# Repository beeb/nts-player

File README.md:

# NTS Web Radio Player

This is a standalone Wi-Fi connected web-radio player based on ESP-32. It was designed for the
[NTS.live](https://www.nts.live/) radio which has 18 live stations (2 main channels + 16 infinite mixtapes).

It's built around the ESP32-S3 and a PCM5122 DAC, with firmware written in Rust and a 3D-printed enclosure. The design
is made to be very simple to interact with: a single encoder with a large knob to select the station and change the
volume.

A ring of LEDs show which station is selected and the current volume level. The click action of the encoder switches
between the modes and allows to put the device to sleep.

Note: this device is not affiliated with NTS or Atonemo which have created a standalone player for NTS. Support your
favorite radio by [becoming a supporter](https://www.nts.live/supporters) or
[buying from the shop](https://shop.nts.live/).

## Features

- Streams MP3 web radio over HTTPS (e.g. NTS: 256 kbps, 44.1 kHz stereo)
- 18 stations on one detented encoder, one click per station
- 18-LED ring around the knob shows the current station (and volume in volume mode)
- Push the knob to toggle station / volume mode, long-press to sleep, press to wake
- Hold the devkit boot button for 5 s to erase all settings (Wi-Fi included) and restart
- Line out at up to about 1.5 Vrms on 3.5 mm and RCA, wired in parallel
  - This is meant as line out, not as headphones output, it expects a load of 1 kOhm or more.
  - The DAC can reach 2.1 Vrms, but the firmware limits the top volume step to -3 dB.
- Low sleep current (about 0.6 mA at 5 V): LED ring and DAC are power-switched in deep sleep
- Home Assistant "off" is a standby that keeps Wi-Fi on and breathes the station LED dimly, press the knob or turn it on
  in HA to wake
- Powered over USB-C (5 V)
- Wi-Fi setup through a portal on the `nts-player` access point
- Home Assistant control (power, station, volume) through the built-in ESPHome integration
- Firmware updates over Wi-Fi from a page on the device, with automatic rollback if the new firmware fails to start

## Repository Layout

```text
firmware/   Rust firmware (ESP-IDF, std)
kicad/      KiCad schematic and PCB for the carrier board
enclosure/  3d-printable enclosure parts
docs/       Datasheet links and devkit pinout
```

## Pin Map

| Function                                              | GPIO      |
| ----------------------------------------------------- | --------- |
| DAC XSMT (soft mute, 10k pull-down)                   | 4         |
| I2S BCK / DIN / LRCK                                  | 5 / 6 / 7 |
| I2C SDA / SCL (4.7k pull-ups to always-on 3V3)        | 8 / 9     |
| Encoder A / B                                         | 10 / 11   |
| Encoder push (wake pin, 10k pull-up to always-on 3V3) | 12        |
| LED ring power enable (10k pull-down)                 | 13        |
| DAC LDO enable (10k pull-down)                        | 14        |
| LED data (via level shifter)                          | 21        |

Avoided: strapping pins 0, 3, 45, 46; GPIO35–37 (octal PSRAM); GPIO19/20 (USB); GPIO38 (onboard RGB LED); GPIO43/44
(UART0).

## Building and Flashing

This is a `std` (ESP-IDF based) Rust project. The ESP-IDF C SDK is downloaded and built automatically by the
`esp-idf-sys` build script. Run all commands from the repository root.

### Prerequisites with Nix

The [flake](./flake.nix) provides a dev shell (x86_64 Linux only) with the Xtensa Rust toolchain from esp-rs (pinned in
[`nix/esp-rust.nix`](./nix/esp-rust.nix)), `ldproxy`, `espflash`, `just`, `jq` and the tools needed by the ESP-IDF
build:

```sh
nix develop
```

### Prerequisites without Nix

Espressif's [Rust on ESP book](https://docs.espressif.com/projects/rust/book/getting-started/index.html) is the
reference for the toolchain setup. TL;DR:

1. Install the
   [ESP-IDF host dependencies](https://docs.espressif.com/projects/esp-idf/en/stable/esp32s3/get-started/linux-macos-setup.html#step-1-install-prerequisites)

2. Install [Rust with `rustup`](https://rustup.rs/).

3. Install [`espup`](https://github.com/esp-rs/espup) and the Xtensa toolchain:

   ```sh
   cargo install espup --locked
   espup install
   ```

4. Activate the environment from `espup`. **This has to be done in every new shell**:

   ```sh
   . $HOME/export-esp.sh
   ```

5. Install the linker wrapper, the flashing tool and the command runner:

   ```sh
   cargo install ldproxy --locked
   cargo install espflash --locked
   cargo install just --locked
   ```

   `ldproxy` is the linker set in [`.cargo/config.toml`](./.cargo/config.toml). Also install `jq` with your package
   manager. `just` runs the commands below, `jq` reads the version in `just export`.

### ESP-IDF

The version is pinned in [`.cargo/config.toml`](./.cargo/config.toml):

```toml
[env]
ESP_IDF_VERSION = "v5.5.5"
```

On the first `cargo build`, the `esp-idf-sys` build script clones that tag into `.embuild/` and downloads the matching
ESP-IDF toolchains. This will take a few GBs of space and take a while the first time.

### Build

```sh
just build
```

Run `just` alone to list all commands.

### Flash and Monitor

Connect the board over USB, then:

```sh
just flash
```

This builds the release firmware, flashes it and opens the serial monitor. `cargo run` does the same through the cargo
`runner` in [`.cargo/config.toml`](./.cargo/config.toml), which calls `just flash-elf`. That recipe also writes the
bootloader built by ESP-IDF (it has app rollback enabled) and the partition table in
[`firmware/partitions.csv`](./firmware/partitions.csv). Plain `espflash flash <elf>` would write espflash's own
bootloader and table and break updates over Wi-Fi. `just monitor` opens the monitor without flashing.

### WSL

Pass the board through to WSL with [usbipd-win](https://github.com/dorssel/usbipd-win). In PowerShell:

```powershell
usbipd list                                         # find the board's bus ID
usbipd bind --busid <BUSID>                         # once, as administrator
usbipd attach --wsl --busid <BUSID> --auto-attach   # each session
```

Your WSL user must be in the `dialout` group to open `/dev/ttyACM0`.

## Firmware Updates over Wi-Fi

### Making a release

1. Bump `version` in [`firmware/Cargo.toml`](./firmware/Cargo.toml).
2. Run `just export`. It builds the release firmware and saves `nts-player-<version>.bin` at the repository root.
3. Send that file.

### Updating a player

1. On the same Wi-Fi as the player, open <http://nts-player.local/>. If the name doesn't resolve, use the IP address of
   the ESP32.
2. Pick the `.bin` file and click Upload. Keep the page open.
3. Playback stops and the LED ring fills up in green. The player restarts with the new firmware, and the page shows the
   new version.

The page rejects files that are not a valid firmware. If the new firmware fails before it connects to Wi-Fi, the next
restart rolls back to the old firmware.

## License

- Hardware (`kicad/`) and enclosure (`enclosure/`): [CC BY-NC-SA 4.0](LICENSE-CC-BY-NC-SA)
- Firmware (`firmware/`): dual-licensed under [MIT](LICENSE-MIT) or [Apache-2.0](LICENSE-APACHE), at your option

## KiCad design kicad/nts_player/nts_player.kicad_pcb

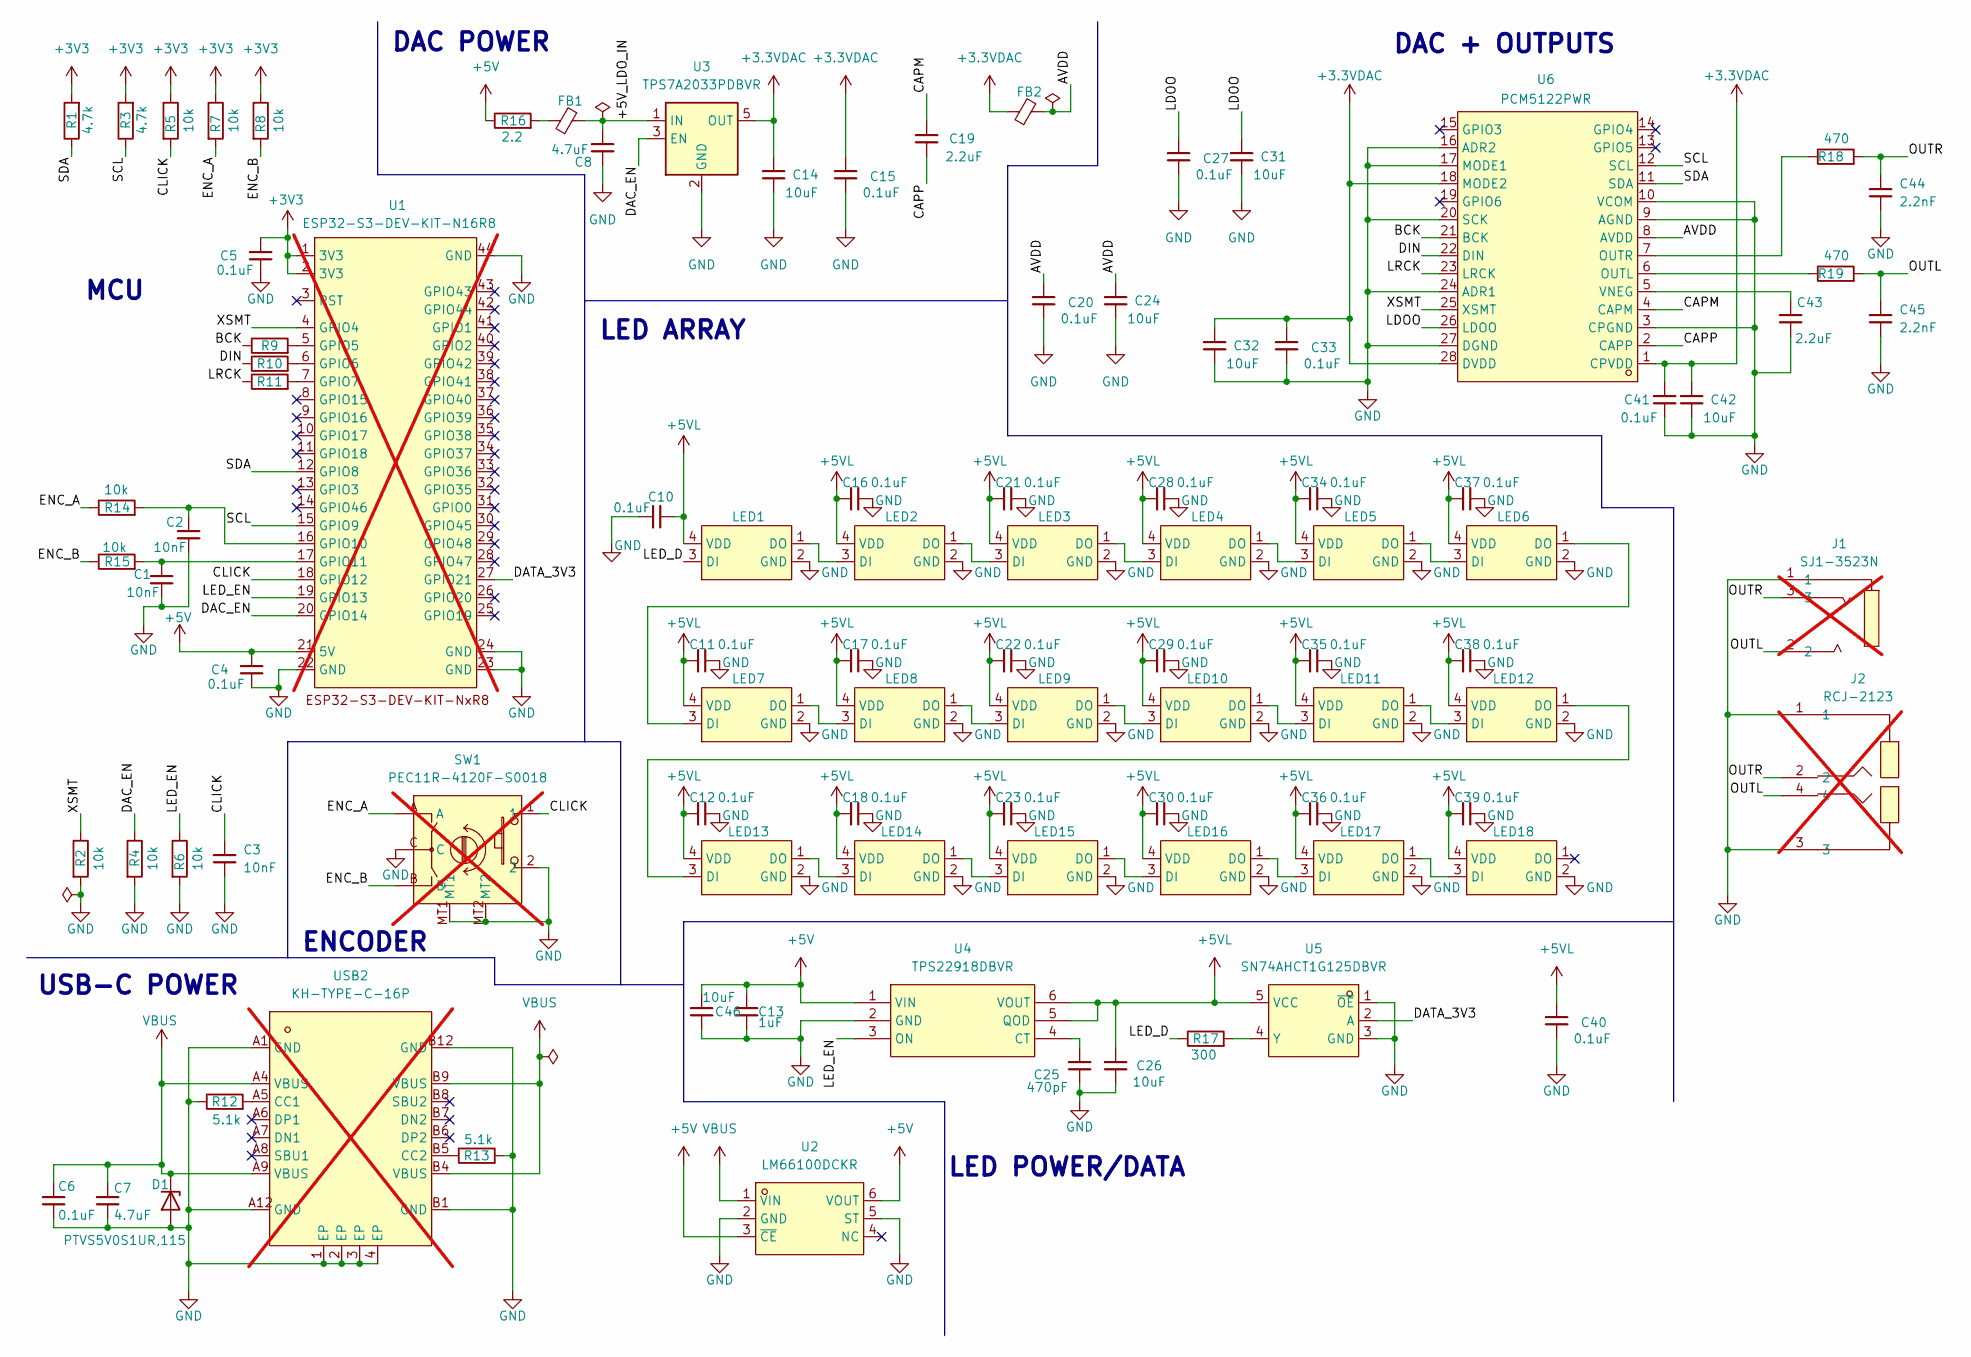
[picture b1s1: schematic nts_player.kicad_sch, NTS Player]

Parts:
C1, C2, C3: 10nF; C0603; MPN 0603B103K500NT; LCSC Part C57112
C4, C5, C6, C10, C11, C12, C15, C16, C17, C18, C20, C21, C22, C23, C27, C28, C29, C30, C33, C34, C35, C36, C37, C38, C39, C40, C41: 0.1uF; C0603; MPN CC0603KRX7R9BB104; LCSC Part C14663
C7, C8: 4.7uF; C0603; MPN CL10A475KO8NNNC; LCSC Part C19666
C13: 1uF; C0603; MPN CL10A105KB8NNNC; LCSC Part C15849
C14, C24, C26, C31, C32, C42, C46: 10uF; C1206; MPN CL31A106KBHNNNE; LCSC Part C13585
C19, C43: 2.2uF; C1206; MPN CL31B225KBHNNNE; LCSC Part C50254
C25: 470pF; C0805; MPN 0805B471K500NT; LCSC Part C1743
C44, C45: 2.2nF; C0805; MPN CL21C222JBFNNNE; LCSC Part C28260
D1: PTVS5V0S1UR,115; SOD-123_L2.8-W1.8-LS3.7-RD; MPN PTVS5V0S1UR,115; LCSC Part C478011
FB1, FB2: GZ1608D601TF; L0603; MPN GZ1608D601TF; LCSC Part C1002
J1: SJ1-3523N; AUDIO-TH_SJ1-3523N; MPN SJ1-3523N; LCSC Part C20182914; not fitted
J2: RCJ-2123; CONN-TH_RCJ-2123; MPN RCJ-2123; LCSC Part C4991847; not fitted
LED1, LED2, LED3, LED4, LED5, LED6, LED7, LED8, LED9, LED10, LED11, LED12, LED13, LED14, LED15, LED16, LED17, LED18: WS2812B-2020-V6; WS2815B-2020-V6; MPN WS2812B-2020-V6; LCSC Part C52917434
R1, R3: 4.7k; R0603; MPN 0603WAF4701T5E; LCSC Part C23162
R2, R4, R5, R6, R7, R8, R14, R15: 10k; R0603; MPN 0603WAF1002T5E; LCSC Part C25804
R9, R10, R11: 33; R0603; MPN 0603WAF330JT5E; LCSC Part C23140
R12, R13: 5.1k; R0603; MPN 0603WAF5101T5E; LCSC Part C23186
R16: 2.2; R0603; MPN 0603WAF220KT5E; LCSC Part C22939
R17: 300; R0603; MPN 0603WAF3000T5E; LCSC Part C23025
R18, R19: 470; R0805; MPN 0805W8F4700T5E; LCSC Part C17710
SW1: PEC11R-4120F-S0018; SW-TH_PEC11R-4XXXF-SXXXX; MPN PEC11R-4120F-S0018; LCSC Part C22402546; not fitted
U1: ESP32-S3-DEV-KIT-N16R8; ESP32-S3-DEV-KIT-NXR8; not fitted
U2: LM66100DCKR; SC-70-6_L2.0-W1.3-P0.65-LS2.1-BL; MPN LM66100DCKR; LCSC Part C2869734
U3: TPS7A2033PDBVR; SOT-23-5; MPN TPS7A2033PDBVR; LCSC Part C2862740
U4: TPS22918DBVR; SOT-23-6_L2.9-W1.6-P0.95-LS2.8-BR; MPN TPS22918DBVR; LCSC Part C131941
U5: SN74AHCT1G125DBVR; SOT-23-5_L3.0-W1.7-P0.95-LS2.8-BR; MPN SN74AHCT1G125DBVR; LCSC Part C7484
U6: PCM5122PWR; TSSOP-28_L9.8-W6.6-P0.65-BL; MPN PCM5122PWR; LCSC Part C962071
USB2: KH-TYPE-C-16P; USB-C-SMD_KH-TYPE-C-16P; MPN KH-TYPE-C-16P; LCSC Part C709357; not fitted

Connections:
+3.3VDAC: C14.2, C15.2, C32.2, C33.2, C41.2, C42.2, FB2.1, U3.5 (OUT), U6.1 (CPVDD), U6.18 (MODE2), U6.28 (DVDD)
+3V3: C5.2, R1.2, R3.2, R5.1, R7.1, R8.1, U1.1 (3V3), U1.2 (3V3)
+5V: C4.2, C13.1, C46.2, R16.1, U1.21 (5V), U2.3 (~CE), U2.6 (VOUT), U4.1 (VIN)
+5VL: C10.1, C11.2, C12.2, C16.2, C17.2, C18.2, C21.2, C22.2, C23.2, C26.2, C28.2, C29.2, C30.2, C34.2, C35.2, C36.2, C37.2, C38.2, C39.2, C40.2, LED1.4 (VDD), LED2.4 (VDD), LED3.4 (VDD), LED4.4 (VDD), LED5.4 (VDD), LED6.4 (VDD), LED7.4 (VDD), LED8.4 (VDD), LED9.4 (VDD), LED10.4 (VDD), LED11.4 (VDD), LED12.4 (VDD), LED13.4 (VDD), LED14.4 (VDD), LED15.4 (VDD), LED16.4 (VDD), LED17.4 (VDD), LED18.4 (VDD), U4.5 (QOD), U4.6 (VOUT), U5.5 (VCC)
/+5V_LDO_IN: C8.1, FB1.2, U3.1 (IN)
/AVDD: C20.2, C24.2, FB2.2, U6.8 (AVDD)
/BCK: R9.1, U6.21 (BCK)
/CAPM: C19.1, U6.4 (CAPM)
/CAPP: C19.2, U6.2 (CAPP)
/CLICK: C3.1, R5.2, SW1.1, U1.18 (GPIO12)
/DAC_EN: R4.1, U1.20 (GPIO14), U3.3 (EN)
/DATA_3V3: U1.27 (GPIO21), U5.2 (A)
/DIN: R10.1, U6.22 (DIN)
/ENC_A: R7.2, R14.1, SW1.A
/ENC_B: R8.2, R15.1, SW1.B
/LDOO: C27.2, C31.2, U6.26 (LDOO)
/LED_D: LED1.3 (DI), R17.1
/LED_EN: R6.1, U1.19 (GPIO13), U4.3 (ON)
/LRCK: R11.1, U6.23 (LRCK)
/OUTL: C45.1, J1.2, J2.4, R19.2
/OUTR: C44.1, J1.3, J2.2, R18.2
/SCL: R3.1, U1.15 (GPIO9), U6.12 (SCL)
/SDA: R1.1, U1.12 (GPIO8), U6.11 (SDA)
/XSMT: R2.1, U1.4 (GPIO4), U6.25 (XSMT)
GND: C1.2, C2.2, C3.2, C4.1, C5.1, C6.1, C7.2, C8.2, C10.2, C11.1, C12.1, C13.2, C14.1, C15.1, C16.1, C17.1, C18.1, C20.1, C21.1, C22.1, C23.1, C24.1, C25.2, C26.1, C27.1, C28.1, C29.1, C30.1, C31.1, C32.1, C33.1, C34.1, C35.1, C36.1, C37.1, C38.1, C39.1, C40.1, C41.1, C42.1, C43.2, C44.2, C45.2, C46.1, D1.2 (A), J1.1, J2.1, J2.3, LED1.2 (GND), LED2.2 (GND), LED3.2 (GND), LED4.2 (GND), LED5.2 (GND), LED6.2 (GND), LED7.2 (GND), LED8.2 (GND), LED9.2 (GND), LED10.2 (GND), LED11.2 (GND), LED12.2 (GND), LED13.2 (GND), LED14.2 (GND), LED15.2 (GND), LED16.2 (GND), LED17.2 (GND), LED18.2 (GND), R2.2, R4.2, R6.2, R12.1, R13.2, SW1.2, SW1.C, SW1.MT1, SW1.MT2, U1.22 (GND), U1.23 (GND), U1.24 (GND), U1.44 (GND), U2.2 (GND), U2.5 (ST), U3.2 (GND), U4.2 (GND), U5.1 (~OE), U5.3 (GND), U6.3 (CPGND), U6.9 (AGND), U6.10 (VCOM), U6.16 (ADR2), U6.17 (MODE1), U6.20 (SCK), U6.24 (ADR1), U6.27 (DGND), USB2.1 (EP), USB2.2 (EP), USB2.3 (EP), USB2.4 (EP), USB2.A1 (GND), USB2.A12 (GND), USB2.B1 (GND), USB2.B12 (GND); also elsewhere on the board
unnamed: FB1.1, R16.2
unnamed: LED1.1 (DO), LED2.3 (DI)
unnamed: LED2.1 (DO), LED3.3 (DI)
unnamed: LED3.1 (DO), LED4.3 (DI)
unnamed: LED4.1 (DO), LED5.3 (DI)
unnamed: LED5.1 (DO), LED6.3 (DI)
unnamed: LED6.1 (DO), LED7.3 (DI)
unnamed: LED7.1 (DO), LED8.3 (DI)
unnamed: LED8.1 (DO), LED9.3 (DI)
unnamed: LED9.1 (DO), LED10.3 (DI)
unnamed: LED10.1 (DO), LED11.3 (DI)
unnamed: LED11.1 (DO), LED12.3 (DI)
unnamed: LED12.1 (DO), LED13.3 (DI)
unnamed: LED13.1 (DO), LED14.3 (DI)
unnamed: LED14.1 (DO), LED15.3 (DI)
unnamed: LED15.1 (DO), LED16.3 (DI)
unnamed: LED16.1 (DO), LED17.3 (DI)
unnamed: LED17.1 (DO), LED18.3 (DI)
unnamed: R9.2, U1.5 (GPIO5)
unnamed: R10.2, U1.6 (GPIO6)
unnamed: R11.2, U1.7 (GPIO7)
unnamed: C2.1, R14.2, U1.16 (GPIO10)
unnamed: C1.1, R15.2, U1.17 (GPIO11)
unnamed: C25.1, U4.4 (CT)
unnamed: R17.2, U5.4 (Y)
unnamed: R19.1, U6.6 (OUTL)
unnamed: R18.1, U6.7 (OUTR)
unnamed: C43.1, U6.5 (VNEG)
unnamed: R12.2, USB2.A5 (CC1)
unnamed: R13.1, USB2.B5 (CC2)
VBUS: C6.2, C7.1, D1.1 (K), U2.1 (VIN), USB2.A4 (VBUS), USB2.A9 (VBUS), USB2.B4 (VBUS), USB2.B9 (VBUS)

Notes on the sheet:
ENCODER
DAC POWER
LED POWER/DATA
MCU
DAC + OUTPUTS
USB-C POWER
LED ARRAY

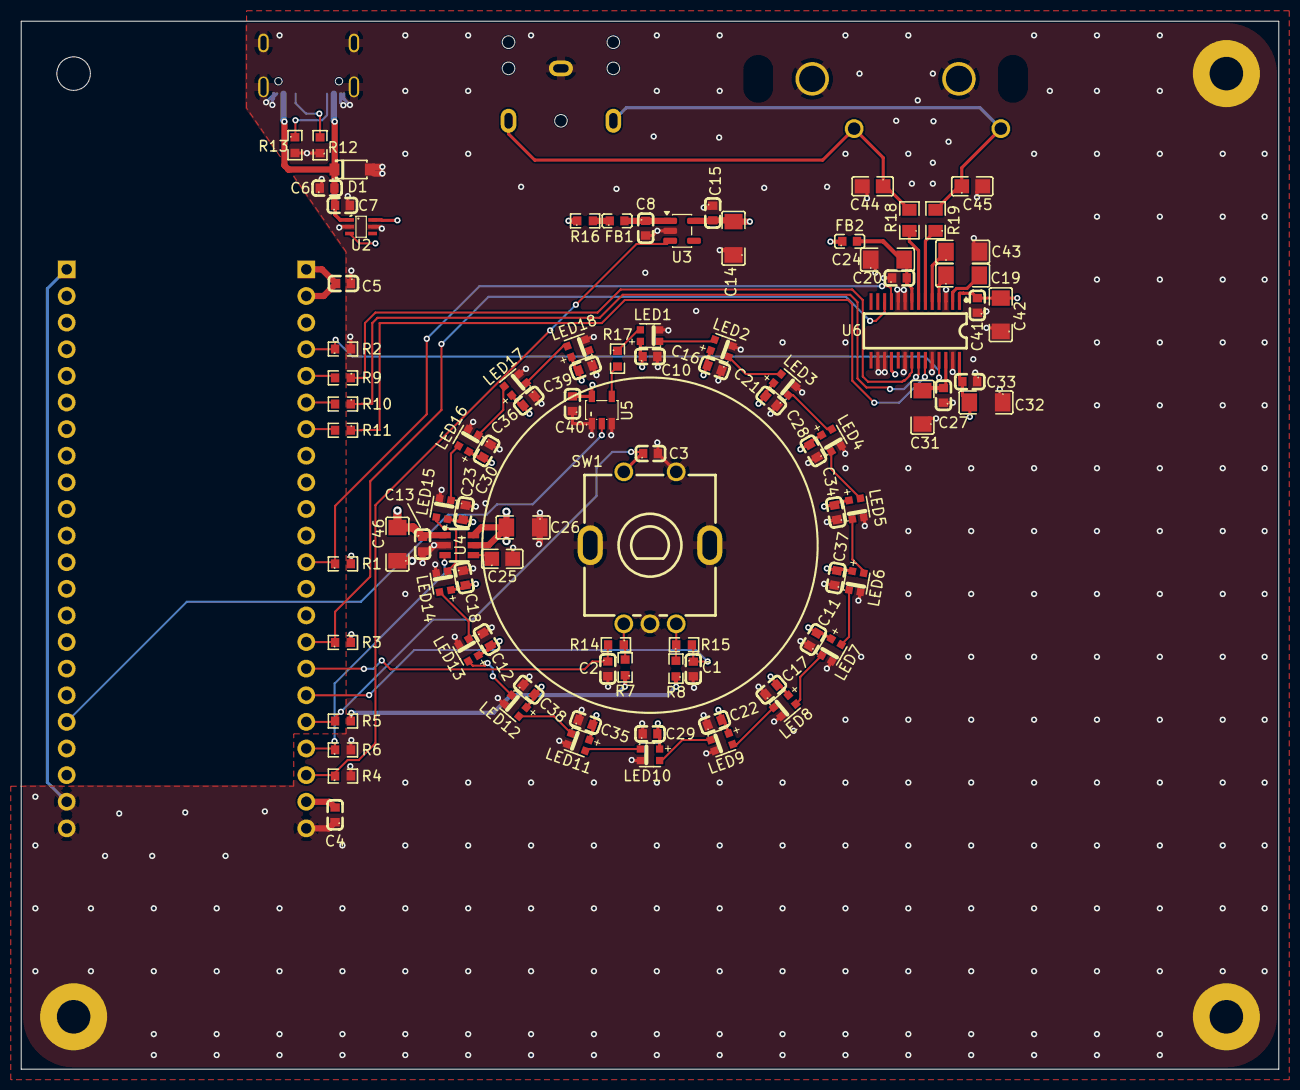
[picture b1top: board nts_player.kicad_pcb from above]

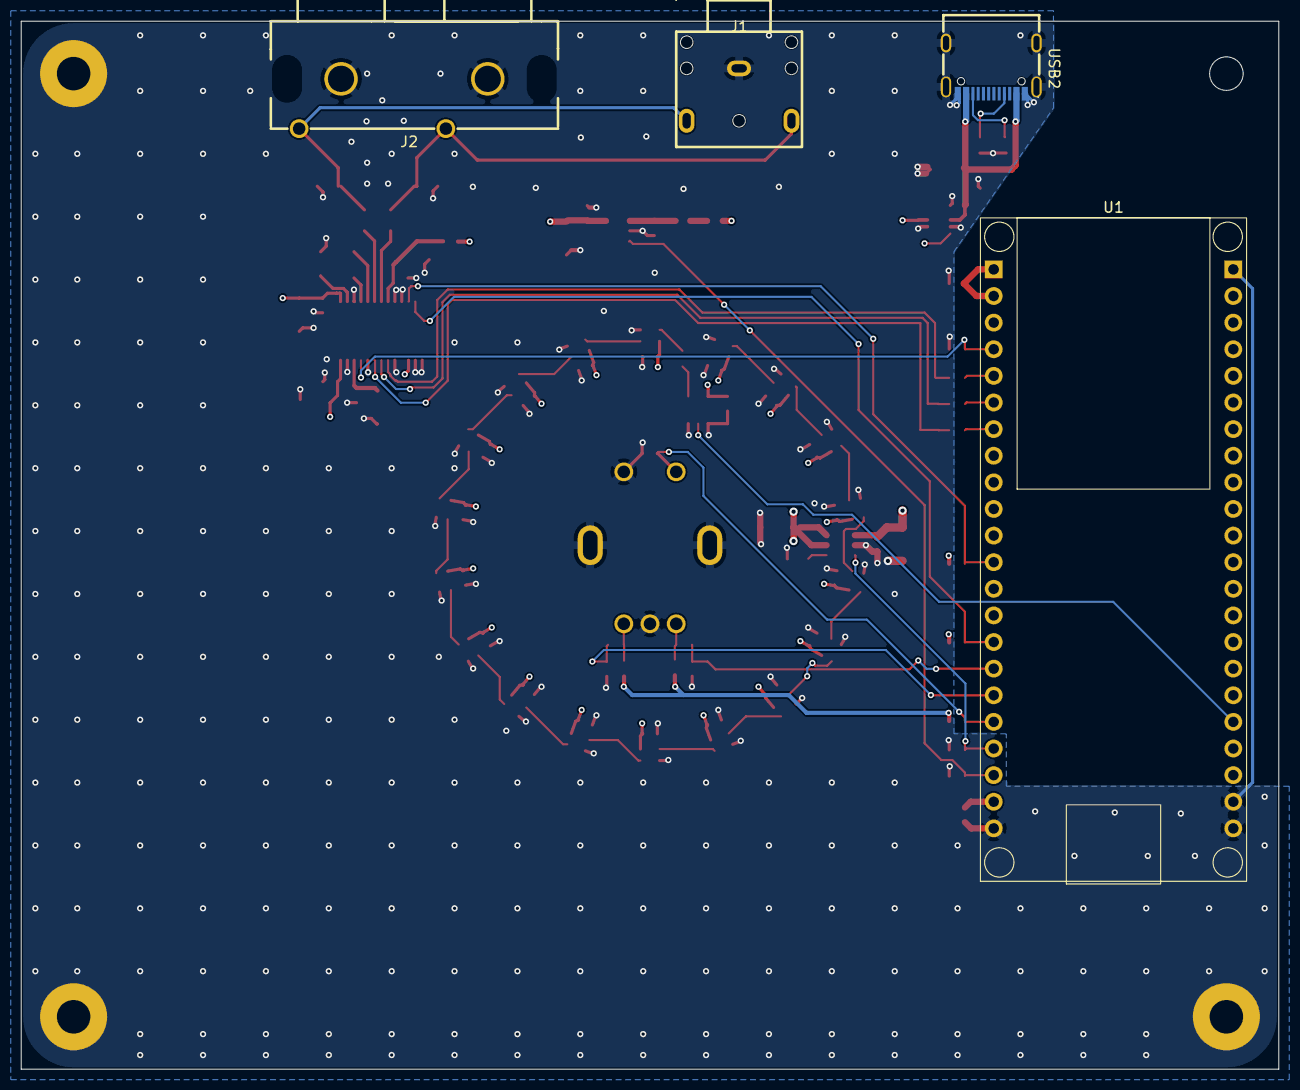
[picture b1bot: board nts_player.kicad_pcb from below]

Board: 4 copper layers, 120.0 x 100.0 mm, 99 parts (4 on the bottom side), 56 nets.

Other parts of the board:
H1: MountingHole_3.2mm_M3
H2, H3, H4: MountingHole_3.2mm_M3_Pad

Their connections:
GND: H2.1, H3.1, H4.1; also elsewhere on the board

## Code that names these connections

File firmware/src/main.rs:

use std::{
    sync::{Arc, Mutex, mpsc},
    thread,
    time::Duration,
};

use anyhow::Result;
use esp_idf_svc::{
    eventloop::EspSystemEventLoop,
    hal::{peripherals::Peripherals, reset::restart},
    nvs::EspDefaultNvsPartition,
    wifi::{BlockingWifi, EspWifi},
};

use crate::{
    api::{Api, Snapshot},
    audio::Player,
    buffer::RingBuffer,
    dac::{Dac, DacPins, I2sPins},
    input::{InputPins, Ui},
    led::{Color, Led, Ring},
    ota::Ota,
    settings::Settings,
    status::{State, Status},
    stream::{Stream, Tuner},
    wifi::Credentials,
};

mod api;
mod audio;
mod buffer;
mod dac;
mod input;
mod led;
mod ota;
mod portal;
mod prelude;
mod settings;
mod status;
mod stream;
mod wifi;

/// Name and version in the image header, the update page checks them.
#[expect(unexpected_cfgs)]
mod app_desc {
    esp_idf_svc::sys::esp_app_desc!();
}

const CONNECT_ATTEMPTS: usize = 3;
const PORTAL_TIMEOUT: Duration = Duration::from_mins(5);
const WIFI_CHECK_INTERVAL: Duration = Duration::from_secs(5);

/// About 5 s of audio at 256 kbps.
const BUFFER_SIZE: usize = 160 * 1024;

fn main() {
    // It is necessary to call this function once. Otherwise, some patches to the runtime
    // implemented by esp-idf-sys might not link properly. See https://github.com/esp-rs/esp-idf-template/issues/71
    esp_idf_svc::sys::link_patches();

    // Bind the log crate to the ESP Logging facilities
    esp_idf_svc::log::EspLogger::initialize_default();

    let mut led = None;
    let status = Arc::new(Status::default());
    if let Err(e) = run(&mut led, &status) {
        log::error!("{e:?}");
        status.set(State::Fatal);
        if let Some(led) = &led {
            led.set(Color::DBG_RED).ok();
        }
        thread::sleep(Duration::from_secs(5));
        restart();
    }
}

/// Run the app, storing the LED in `led` so that `main` can still use it on error.
#[expect(
    clippy::too_many_lines,
    reason = "the startup sequence reads best in one place"
)]
fn run(led: &mut Option<Arc<Led>>, status: &Arc<Status>) -> Result<()> {
    let peripherals = Peripherals::take()?;
    let led = led.insert(Arc::new(Led::new(peripherals.pins.gpio38)?));
    let nvs = EspDefaultNvsPartition::take()?;
    let settings = Settings::load(nvs.clone())?;
    let tuner = Arc::new(Tuner::new(settings.station));
    let buffer = Arc::new(RingBuffer::new(BUFFER_SIZE));
    let dac = Arc::new(Dac::new(
        DacPins {
            en: peripherals.pins.gpio14.degrade_output(),
            xsmt: peripherals.pins.gpio4.degrade_output(),
            i2c: peripherals.i2c0,
            sda: peripherals.pins.gpio8.degrade_input_output(),
            scl: peripherals.pins.gpio9.degrade_input_output(),
            i2s: I2sPins {
                i2s: peripherals.i2s0,
                bck: peripherals.pins.gpio5.degrade_input_output(),
                din: peripherals.pins.gpio6.degrade_output(),
                lrck: peripherals.pins.gpio7.degrade_input_output(),
            },
        },
        settings.volume,
    )?);
    let snapshot = Arc::new(Mutex::new(Snapshot::new(settings)));
    let (commands_tx, commands_rx) = mpsc::channel();
    Ui::spawn(
        InputPins {
            enc_a: peripherals.pins.gpio10.degrade_input(),
            enc_b: peripherals.pins.gpio11.degrade_input(),
            push: peripherals.pins.gpio12.degrade_input(),
            boot: peripherals.pins.gpio0.degrade_input(),
        },
        led.clone(),
        Ring::new(peripherals.pins.gpio21, peripherals.pins.gpio13)?,
        tuner.clone(),
        buffer.clone(),
        dac.clone(),
        status.clone(),
        settings,
        snapshot.clone(),
        commands_rx,
        nvs.clone(),
    )?;
    let sysloop = EspSystemEventLoop::take()?;
    let mut wifi = BlockingWifi::wrap(
        EspWifi::new(peripherals.modem, sysloop.clone(), Some(nvs.clone()))?,
        sysloop,
    )?;

    let Some(mut creds) = Credentials::load(nvs.clone())? else {
        log::info!("no wifi credentials saved");
        led.set(Color::DBG_BLUE)?;
        status.set(State::Portal);
        return portal::run(wifi, nvs, None); // stay on portal forever
    };
    led.set(Color::DBG_YELLOW)?;
    let connected = (1..=CONNECT_ATTEMPTS).any(|attempt| {
        creds
            .connect(&mut wifi)
            .inspect_err(|e| {
                log::warn!(
                    "connection attempt {attempt} to {} failed: {e:?}",
                    creds.ssid
                );
            })
            .is_ok()
    });
    if !connected {
        // connecting with saved credentials failed, let's show the portal
        // again for a little bit before we retry
        led.set(Color::DBG_BLUE)?;
        status.set(State::Portal);
        return portal::run(wifi, nvs, Some(PORTAL_TIMEOUT));
    }
    led.set(Color::DBG_GREEN)?;
    status.set(State::Online);
    log::info!(
        "connected to {}, ip: {}",
        creds.ssid,
        wifi.wifi().sta_netif().get_ip_info()?.ip
    );
    if let Err(e) = creds.save_channel(nvs.clone(), &wifi) {
        log::warn!("could not save wifi channel: {e:?}");
    }

    Stream::spawn(tuner, buffer.clone(), status.clone(), nvs)?;
    Player::spawn(buffer, dac)?;
    if let Err(e) = Api::spawn(wifi.wifi().sta_netif(), snapshot, commands_tx.clone()) {
        log::warn!("could not start the API, playing anyway: {e:?}");
    }
    // keep the server alive in the loop below
    let _ota = Ota::start(commands_tx)
        .inspect_err(|e| log::warn!("could not start the update page, playing anyway: {e:?}"));
    // keep `wifi` alive and reconnect it when the link drops
    loop {
        thread::sleep(WIFI_CHECK_INTERVAL);
        if wifi.is_connected()? {
            continue;
        }
        log::warn!("wifi down, reconnecting");
        status.set(State::Connecting);
        if let Err(e) = creds.connect(&mut wifi) {
            log::warn!("wifi reconnect failed: {e:?}");
            // the router may have moved to another channel
            creds.channel = None;
        } else {
            log::info!("wifi reconnected");
            status.set(State::Online);
        }
    }
}
